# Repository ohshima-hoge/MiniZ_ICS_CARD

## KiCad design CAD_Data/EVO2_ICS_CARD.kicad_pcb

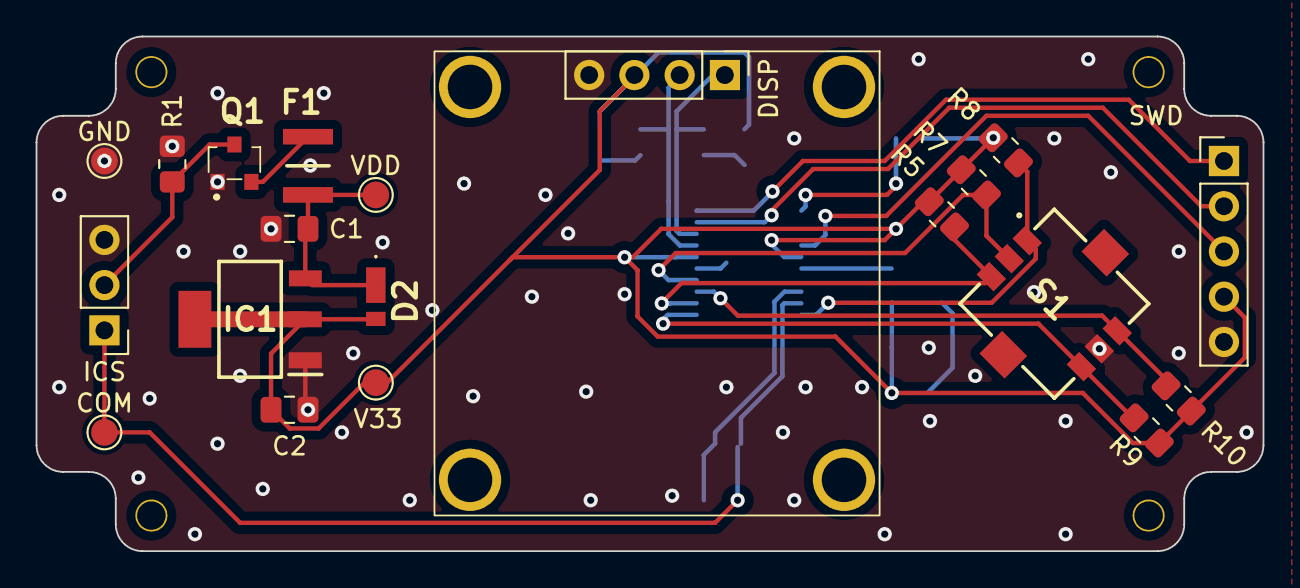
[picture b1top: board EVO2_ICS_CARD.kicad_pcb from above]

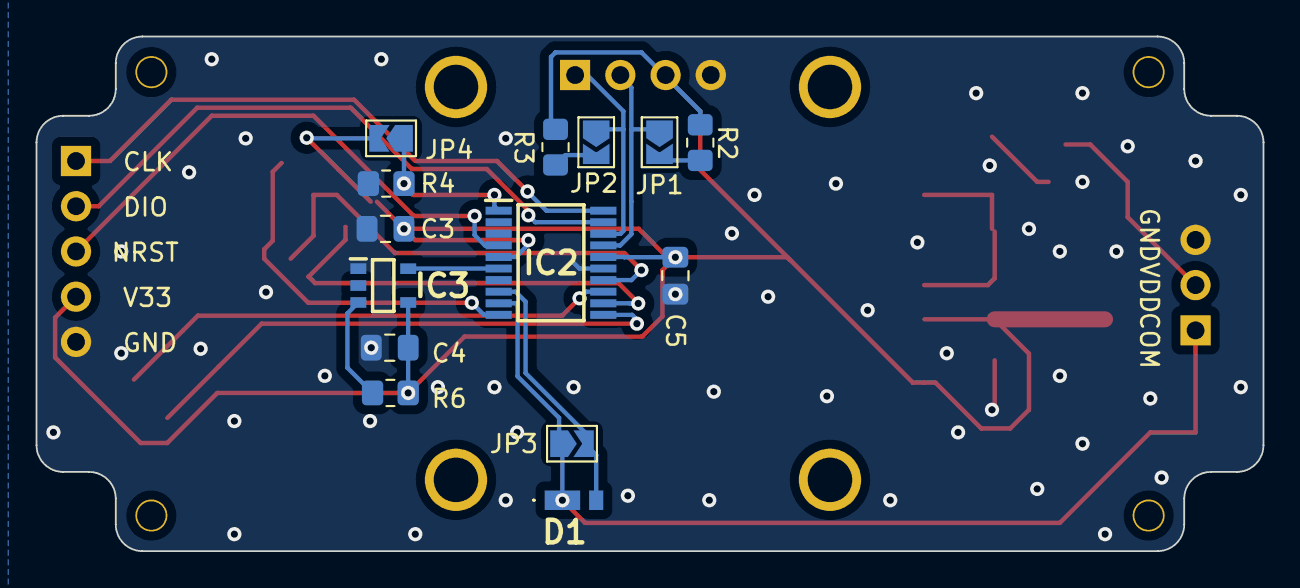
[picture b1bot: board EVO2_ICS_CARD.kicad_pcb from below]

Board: 2 copper layers, 68.9 x 28.9 mm, 34 parts (14 on the bottom side), 22 nets.

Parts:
C1, C2: 10u; C_0805_2012Metric_Pad1.18x1.45mm_HandSolder
C3, C4, C5: 0.1u; C_0805_2012Metric_Pad1.18x1.45mm_HandSolder
COM: TestPoint; TestPoint_Pad_D1.5mm
D1, D2: CUHS20F30,H3F; CUHS20F30H3F
DISP: DISP; PinHeader_1x04_P2.54mm_Vertical
F1: MF-USMF010-2; FUSC3226X110N
GND: TestPoint; TestPoint_Pad_D1.5mm
IC1: AZ1117CH-3.3TRG1; SOT230P700X180-4N
IC2: STM32L010F4P6; SOP65P640X120-20N
IC3: SIT2001BI-S2-33E-12.000000G; SOT95P280X130-5N
ICS: I.C.S; PinHeader_1x03_P2.54mm_Vertical
JP1, JP2, JP3, JP4: SolderJumper_2_Open; SolderJumper-2_P1.3mm_Open_TrianglePad1.0x1.5mm
Q1: SSM3J332R,LF; SSM3J332RLFT
R1: 100k; R_0805_2012Metric_Pad1.20x1.40mm_HandSolder
R2, R3: 3.3k; R_0805_2012Metric_Pad1.20x1.40mm_HandSolder
R4, R5, R6, R7, R8, R9, R10: 10k; R_0805_2012Metric_Pad1.20x1.40mm_HandSolder
S1: SKRHAAE010
SWD: SWD; PinHeader_1x05_P2.54mm_Vertical
V33: TestPoint; TestPoint_Pad_D1.5mm
VDD: TestPoint; TestPoint_Pad_D1.5mm

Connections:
+3.3V: C2.1, C3.1, C4.1, C5.1, D2.2 (A), DISP.2, IC1.2 (OUTPUT), IC1.4 (VOUT), IC2.5 (VDDA), IC2.16 (VDD), IC3.4 (VDD), JP4.2 (B), R2.1, R3.1, R5.1, R6.1, R7.1, R8.1, R9.1, R10.1, SWD.4, V33.1
/CLK: IC2.6 (PA0-CK_IN), IC3.5 (OUT)
/NRST: IC2.4 (NRST), SWD.3
/RX: COM.1, D1.1 (K), IC2.9 (PA3), ICS.1, JP3.1 (A)
/SCL: DISP.3, IC2.17 (PA9), JP1.1 (A)
/SDA: DISP.4, IC2.18 (PA10), JP2.1 (A)
/SWCLK: IC2.20 (PA14), SWD.1
/SWDIO: IC2.19 (PA13), SWD.2
/SW_DOWN: IC2.11 (PA5), R9.2, S1.6 (D)
/SW_LEFT: IC2.12 (PA6), R5.2, S1.3 (C)
/SW_PUSH: IC2.14 (PB1), R7.2, S1.2 (CENTER_PUSH)
/SW_RIGHT: IC2.13 (PA7), R10.2, S1.4 (B)
/SW_UP: IC2.10 (PA4), R8.2, S1.1 (A)
/TX: D1.2 (A), IC2.8 (PA2), JP3.2 (B)
GND: C1.2, C2.2, C3.2, C4.2, C5.2, DISP.1, GND.1, IC1.1 (ADJ/GND), IC2.15 (VSS), IC3.1 (GND), ICS.3, Q1.1 (G), R1.2, R4.2, S1.5 (COMMON), SWD.5
unnamed: IC2.1 (PB9-BOOT0), JP4.1 (A), R4.1
unnamed: IC3.3 (OE/~ST/NC), R6.2
unnamed: ICS.2, Q1.3 (D), R1.1
unnamed: JP1.2 (B), R2.2
unnamed: JP2.2 (B), R3.2
unnamed: F1.1, Q1.2 (S)
VDD: C1.1, D2.1 (K), F1.2, IC1.3 (INPUT), VDD.1

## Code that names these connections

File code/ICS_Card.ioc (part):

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Mcu.Name=STM32L010F4Px
Mcu.Package=TSSOP20
Mcu.UserName=STM32L010F4Px
PA0-CK_IN.Mode=HSE-External-Clock-Source-for-TinyNemo
PA0-CK_IN.Signal=RCC_CK_IN
PA10.Mode=I2C
PA10.Signal=I2C1_SDA
PA13.Mode=Serial_Wire
PA13.Signal=SYS_SWDIO
PA14.Mode=Serial_Wire
PA14.Signal=SYS_SWCLK
PA2.Mode=Asynchronous
PA2.Signal=USART2_TX
PA3.Mode=Asynchronous
PA3.Signal=USART2_RX
PA4.GPIOParameters=GPIO_ModeDefaultEXTI
PA4.GPIO_ModeDefaultEXTI=GPIO_MODE_IT_FALLING
PA4.Signal=GPXTI4
PA5.GPIOParameters=GPIO_ModeDefaultEXTI
PA5.GPIO_ModeDefaultEXTI=GPIO_MODE_IT_FALLING
PA5.Signal=GPXTI5
PA6.GPIOParameters=GPIO_ModeDefaultEXTI
PA6.GPIO_ModeDefaultEXTI=GPIO_MODE_IT_FALLING
PA6.Signal=GPXTI6
PA7.GPIOParameters=GPIO_ModeDefaultEXTI
PA7.GPIO_ModeDefaultEXTI=GPIO_MODE_IT_FALLING
PA7.Signal=GPXTI7
PA9.Mode=I2C
PA9.Signal=I2C1_SCL
PB1.GPIOParameters=GPIO_ModeDefaultEXTI
PB1.GPIO_ModeDefaultEXTI=GPIO_MODE_IT_FALLING
PB1.Signal=GPXTI1
RCC.HSE_VALUE=12000000
RCC.SYSCLKFreq_VALUE=32000000
RCC.SYSCLKSource=RCC_SYSCLKSOURCE_PLLCLK
board=custom

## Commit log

2024-01-24 Create CAD
